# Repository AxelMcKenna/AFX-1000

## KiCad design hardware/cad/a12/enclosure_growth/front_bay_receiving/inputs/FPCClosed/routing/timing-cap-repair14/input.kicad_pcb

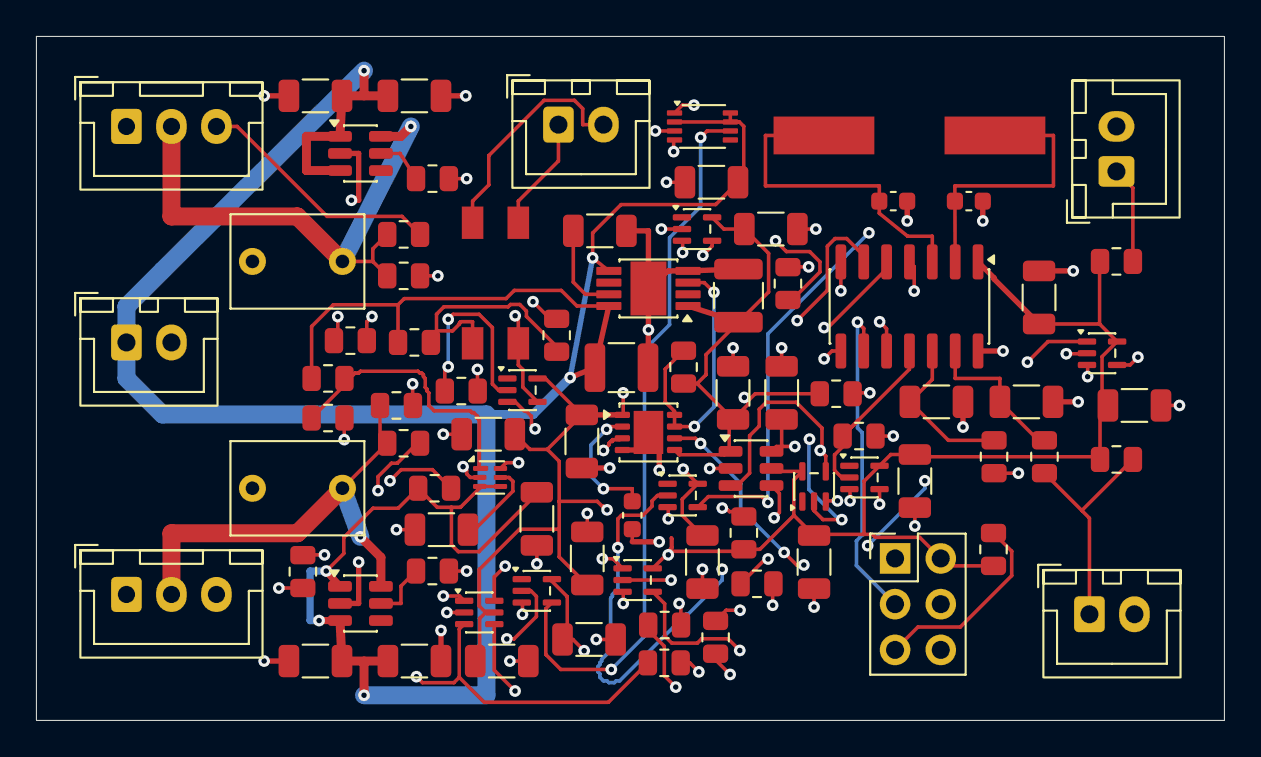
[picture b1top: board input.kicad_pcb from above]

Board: 4 copper layers, 66.0 x 38.0 mm, 84 parts (0 on the bottom side), 45 nets.

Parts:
C1, C2: 10uF 25V C3225X7R1E106K250AC; Capacitor_SMD__C_1210_3225Metric
C3, C14, C22, C23: 10nF 50V C0G C1206C103J5GACTU; Capacitor_SMD__C_1206_3216Metric
C4, C5, C6, C8, C9, C10, C11, C12, C13, C15, C16, C17, C18, C19, C24: 100nF 25V C0G C1206C104J3GACTU; Capacitor_SMD__C_1206_3216Metric
C7: 2.7nF 50V C0G5% C0603C272J5GACTU; Capacitor_SMD__C_0603_1608Metric
C20, C21: 15pF 50V C0G5% C0603C150J5GACTU; Capacitor_SMD__C_0603_1608Metric
C201, C202, C301, C302: 100nF25V C0G5% C1206C104J3GACTU; Capacitor_SMD__C_1206_3216Metric
C203, C303: 1uF63V10% WIMA MKS2C041001F00KSSD; Capacitor_THT__C_Rect_L7.2mm_W5.0mm_P5.00mm
J2, J3, J4, J201: JST B2B-XH-A / XHP-2 / SXH-001T-P0.6; Connector_JST__JST_XH_B2B-XH-A_1x02_P2.50mm_Vertical
J5: AVRISP2x3 target-powered3.3V sense ONLY; Connector_PinHeader_2.54mm__PinHeader_2x03_P2.54mm_Vertical
J202, J203: JST B3B-XH-A / XHP-3 / SXH-001T-P0.6; Connector_JST__JST_XH_B3B-XH-A_1x03_P2.50mm_Vertical
R1, R16, R17, R21, R23: 1k 0.1%25ppm TNPW08051K00BEEA; Resistor_SMD__R_0805_2012Metric
R2, R6, R10, R13, R202, R302: 10k 0.1%25ppm TNPW080510K0BEEA; Resistor_SMD__R_0805_2012Metric
R3, R4, R5, R7, R14, R15: 47k 0.1%25ppm TNPW080547K0BEEA; Resistor_SMD__R_0805_2012Metric
R8: 68k 0.1%25ppm TNPW080568K0BEEA; Resistor_SMD__R_0805_2012Metric
R9: 39k 0.1%25ppm TNPW080539K0BEEA; Resistor_SMD__R_0805_2012Metric
R11: 56.2k 0.1%25ppm TNPW080556K2BEEA; Resistor_SMD__R_0805_2012Metric
R12, R24, R201, R203, R301, R303: 100k 0.1%25ppm TNPW0805100KBEEA; Resistor_SMD__R_0805_2012Metric
R20, R22: 20k 0.1%25ppm TNPW080520K0BEEA; Resistor_SMD__R_0805_2012Metric
U1: ATtiny84A-SSUR; Package_SO__SOIC-14_3.9x8.7mm_P1.27mm
U2: TPS7A1633DGNR; TI_DGN0008C
U3: SN74LVC2G17DCKR; Package_TO_SOT_SMD__SOT-363_SC-70-6
U4: TPS3431SDRBR; Package_SON__VSON-8-1EP_3x3mm_P0.65mm_EP1.65x2.4mm
U5: SN74AUP1G17DCKR; Package_TO_SOT_SMD__SOT-353_SC-70-5
U6: SN74LVC1T45DBVR; Package_TO_SOT_SMD__SOT-23-6
U7: SN74LVC1G14DCKR; Package_TO_SOT_SMD__SOT-353_SC-70-5
U8: SN74LVC1G74DCUR; TI_DCU0008A
U9: TPS389001DSET; Package_SON__WSON-6_1.5x1.5mm_P0.5mm
U10, U11: SN74LVC1G17DCKR; Package_TO_SOT_SMD__SOT-353_SC-70-5
U12, U13: SN74LVC1G08DCKR; Package_TO_SOT_SMD__SOT-353_SC-70-5
U14: SN74LVC1G06DCKR; Package_TO_SOT_SMD__SOT-353_SC-70-5
U15: TLP175A(TPL,E); RMX_FH02__TLP175A_11-4M1S_Receiving
U16: SN74LVC1G34DCKR; Package_TO_SOT_SMD__SOT-353_SC-70-5
U201, U301: TPS2553DBVR-1; Package_TO_SOT_SMD__SOT-23-6
X1: ABLS-4.000MHZ-12-D4Y-T; RMX_FH02__ABLS_Manufacturer_Land

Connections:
/E28_POWER_RUN: J4.2, U15.6
/FAN5V_IN: C1.1, C10.1, C11.1, C12.1, C13.1, C15.1, C201.1, C202.1, C301.1, C302.1, J201.1, R1.1, R10.1, R11.1, U2.5, U2.8, U6.6, U7.5, U8.2, U8.7, U8.8, U9.3, U9.4, U10.5, U201.1, U201.3, U301.1, U301.3
/FAN_L_5V: C203.1, J202.2, R202.1, R203.1, U201.6
/FAN_L_ILIM: R201.1, U201.5
/FAN_L_TACH: J202.3, R14.1, R202.2, U3.1
/FAN_R_5V: C303.1, J203.2, R302.1, R303.1, U301.6
/FAN_R_ILIM: R301.1, U301.5
/FAN_R_TACH: J203.3, R15.1, R302.2, U3.3
/FAULT_CLK: U7.4, U8.1
/GND: C1.2, C2.2, C3.2, C4.2, C5.2, C6.2, C7.2, C8.2, C9.2, C10.2, C11.2, C12.2, C13.2, C14.2, C15.2, C16.2, C17.2, C18.2, C19.2, C20.2, C21.2, C22.2, C23.2, C24.2, C201.2, C202.2, C203.2, C301.2, C302.2, C303.2, J2.2, J3.2, J5.6, J201.2, J202.1, J203.1, R3.2, R4.2, R8.2, R9.2, R12.2, R13.2, R14.2, R15.2, R24.2, R201.2, R203.2, R301.2, R303.2, U1.14, U2.4, U2.9, U3.2, U4.4, U4.9, U5.3, U6.2, U7.3, U8.4, U9.2, U10.3, U11.3, U12.3, U13.3, U14.3, U16.3, U201.2, U301.2
/HEALTH_AND_WD: U12.4, U13.1
/HEARTBEAT: R4.1, U1.11, U16.2
/HEARTBEAT_FAST: U4.6, U16.4
/HW_NOFAULT: U11.4, U13.2
/HW_NOFAULT_5: R9.1, U8.3, U11.2
/ISP_MISO: J5.1, U1.8
/ISP_MOSI: J5.4, U1.7
/ISP_SCK: J5.3, U1.9
/LDO_DELAY: C3.1, U2.7
/LEAF_PERMISSION: R13.1, U13.4, U14.2
/LED_A: R1.2, R2.1, U15.1
/LED_K: R2.2, U14.4, U15.3
/MCU_HEALTH: R3.1, U1.6, U12.1
/MCU_RESET_N: J5.5, R6.2, U1.4
/MCU_TACH_L: R16.2, U1.10
/MCU_TACH_R: R17.2, U1.5
/P03_POWER_RUN: J4.1, U15.4
/RAW_CLEAR_FAST: U8.6, U10.4
/RAW_CLEAR_N: R10.2, U9.6, U10.2
/RAW_POR_CT: C14.1, U9.5
/RAW_POR_SENSE: R11.2, R12.1, U9.1
/TACH_L_BUF: R16.1, U3.6
/TACH_R_BUF: R17.1, U3.4
/TEMP_L_ADC: C22.1, R21.2, U1.13
/TEMP_L_NODE: J2.1, R20.2, R21.1
/TEMP_R_ADC: C23.1, R23.2, U1.12
/TEMP_R_NODE: J3.1, R22.2, R23.1
/V3V3: C2.1, C4.1, C5.1, C6.1, C8.1, C9.1, C16.1, C17.1, C18.1, C19.1, C24.1, J5.2, R5.1, R6.1, R7.1, R20.1, R22.1, R24.1, U1.1, U2.1, U3.5, U4.1, U4.5, U5.5, U6.1, U6.5, U11.5, U12.5, U13.5, U14.5, U16.5
/WD_CWD: C7.1, U4.2
/WD_EN: R7.2, U4.3
/WD_OK: R5.2, U2.3, U4.7, U4.8, U5.2
/WD_OK_5: R8.1, U6.4, U7.2
/WD_OK_FAST: U5.4, U6.3, U12.2
/XTAL1: C20.1, U1.2, X1.1
/XTAL2: C21.1, U1.3, X1.2

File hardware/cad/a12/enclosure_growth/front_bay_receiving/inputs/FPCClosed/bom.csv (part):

Reference,Part_or_value,Footprint,Source,Note
U1,ATtiny84A-SSUR,FPC01:Package_SO__SOIC-14_3.9x8.7mm_P1.27mm,https://ww1.microchip.com/downloads/en/DeviceDoc/ATtiny24A-4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,"Microchip DS40002269A source bytes captured. External4MHz crystal; CPU4MHz, Timer1/8, ADC/64 per captured root firmware. 3mA VCC-pin current is receiving, NOT a transferable bare-external-clock table guarantee."
U2,TPS7A1633DGNR,FPC01:TI_DGN0008C,https://www.ti.com/lit/ds/symlink/tps7a16.pdf,"Fixed output: pin2 MUST remain unconnected. PG joins open-drain WD_OK; rising85..95% output threshold is not a precision3.3V monitor. All regulator caps same FRONT face, local direct ground in future layout."
U3,SN74LVC2G17DCKR,FPC01:Package_TO_SOT_SMD__SOT-363_SC-70-6,https://www.ti.com/lit/ds/symlink/sn74lvc2g17.pdf,5.5V tolerant Schmitt inputs/Ioff. Fan-side pullups follow switched5V in FP01; no always-on pullup phantom-feed.
U4,TPS3431SDRBR,FPC01:Package_SON__VSON-8-1EP_3x3mm_P0.65mm_EP1.65x2.4mm,https://www.ti.com/lit/ds/symlink/tps3431.pdf,"TI permits tying ENOUT/WDO. Timeout independently blocks permission and clocksRAW5latch; it doesNOTdriveMCURESET, because startupENOUTLOW would createEXTRF and conflictwithcleanPOR firmware. Watchdogretry MUST NOT reclosecontact."
U5,SN74AUP1G17DCKR,FPC01:Package_TO_SOT_SMD__SOT-353_SC-70-5,https://www.ti.com/lit/ds/symlink/sn74aup1g17.pdf,
U6,SN74LVC1T45DBVR,FPC01:Package_TO_SOT_SMD__SOT-23-6,https://www.ti.com/lit/ds/symlink/sn74lvc1t45.pdf,A-to-B; either supply atGND isolates both ports. RAW5 B pulldown forces fault on complete3.3V loss; intermediate-rail behavior remains receiving.
U7,SN74LVC1G14DCKR,FPC01:Package_TO_SOT_SMD__SOT-353_SC-70-5,https://www.ti.com/lit/ds/symlink/sn74lvc1g14.pdf,
U8,SN74LVC1G74DCUR,FPC01:TI_DCU0008A,https://www.ti.com/lit/ds/symlink/sn74lvc1g74.pdf,IndependentRAW5-powered positive-edge latch; D=1. First watchdog failure storesQ=1/Q_N=0 until RAW5 power-cycle clear. 3.3V-only resets cannot intentionally clear it.
U9,TPS389001DSET,FPC01:Package_SON__WSON-6_1.5x1.5mm_P0.5mm,https://www.ti.com/lit/ds/symlink/tps3890.pdf,"Dedicatedrawpower-cycle clear nominal1.7963V; assertion/deassertion and1.65V latch retention crossover must be characterized. CT delays clear RELEASE, not fault capture."
U10,SN74LVC1G17DCKR,FPC01:Package_TO_SOT_SMD__SOT-353_SC-70-5,https://www.ti.com/lit/ds/symlink/sn74lvc1g17.pdf,
U11,SN74LVC1G17DCKR,FPC01:Package_TO_SOT_SMD__SOT-353_SC-70-5,https://www.ti.com/lit/ds/symlink/sn74lvc1g17.pdf,
U12,SN74LVC1G08DCKR,FPC01:Package_TO_SOT_SMD__SOT-353_SC-70-5,https://www.ti.com/lit/ds/symlink/sn74lvc1g08.pdf,2.0V VIH applies over actual3.0..3.6V supply row. All inputs have active push-pull drivers; rawopen-drain WD_OK is Schmittconditioned first.
U13,SN74LVC1G08DCKR,FPC01:Package_TO_SOT_SMD__SOT-353_SC-70-5,https://www.ti.com/lit/ds/symlink/sn74lvc1g08.pdf,2.0V VIH applies over actual3.0..3.6V supply row. All inputs have active push-pull drivers; rawopen-drain WD_OK is Schmittconditioned first.
U14,SN74LVC1G06DCKR,FPC01:Package_TO_SOT_SMD__SOT-353_SC-70-5,https://www.ti.com/lit/ds/symlink/sn74lvc1g06.pdf,
U16,SN74LVC1G34DCKR,FPC01:Package_TO_SOT_SMD__SOT-353_SC-70-5,https://www.ti.com/lit/ds/symlink/sn74lvc1g34.pdf,
U15,"TLP175A(TPL,E)",FPC01:RMX_FH02__TLP175A_11-4M1S_Receiving,https://toshiba.semicon-storage.com/info/TLP175A_datasheet_e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,Normally-open isolated contact ONLY P03J106.3→E28J5.3. 1/3LED and4/6contact exact pins. Recommendedambient≤65°C. No E28_MASTER_ENABLE connection.
X1,ABLS-4.000MHZ-12-D4Y-T,FPC01:RMX_FH02__ABLS_Manufacturer_Land,https://abracon.com/Resonators/abls.pdf,4MHzfundamental/CL12pF/−40..85C/initial±30ppm/temp±30ppm. Manufacturerland5.6x2.1mm/9.5mmcentres. 15pF+15pF assumes4.5pFstray; drive/startup/complete±0.1%clock requires receiving tests.
R1,1k 0.1%25ppm TNPW08051K00BEEA,FPC01:Resistor_SMD__R_0805_2012Metric,https://www.vishay.com/docs/28758/tnpw_e3.pdf,Complete±3%; feed branch includes shunt current once.
R2,10k 0.1%25ppm TNPW080510K0BEEA,FPC01:Resistor_SMD__R_0805_2012Metric,https://www.vishay.com/docs/28758/tnpw_e3.pdf,"Complete±3%; across LED, not merely gate pulldown. Ioff10uA creates≤.103VLED in settled model."
R3,47k 0.1%25ppm TNPW080547K0BEEA,FPC01:Resistor_SMD__R_0805_2012Metric,https://www.vishay.com/docs/28758/tnpw_e3.pdf,DefaultOFF duringMCUreset/input state.
R4,47k 0.1%25ppm TNPW080547K0BEEA,FPC01:Resistor_SMD__R_0805_2012Metric,https://www.vishay.com/docs/28758/tnpw_e3.pdf,No floatingWDI whileMCUreset.
R5,47k 0.1%25ppm TNPW080547K0BEEA,FPC01:Resistor_SMD__R_0805_2012Metric,https://www.vishay.com/docs/28758/tnpw_e3.pdf,Open-drainwatchdog/PG pullup.
R6,10k 0.1%25ppm TNPW080510K0BEEA,FPC01:Resistor_SMD__R_0805_2012Metric,https://www.vishay.com/docs/28758/tnpw_e3.pdf,MCURESET externalpullup; internal30..60k table at5.5V is not our full3.3V bound. ExternalwatchdogdoesNOTdriveRESET; avoidsstartupEXTRF.
R7,47k 0.1%25ppm TNPW080547K0BEEA,FPC01:Resistor_SMD__R_0805_2012Metric,https://www.vishay.com/docs/28758/tnpw_e3.pdf,WDalwaysenabled; manufacturing must not leave bypass fitted.
R8,68k 0.1%25ppm TNPW080568K0BEEA,FPC01:Resistor_SMD__R_0805_2012Metric,https://www.vishay.com/docs/28758/tnpw_e3.pdf,Complete±3%; 1T45off2uA+G14input5uA gives≤.49028V.
R9,39k 0.1%25ppm TNPW080539K0BEEA,FPC01:Resistor_SMD__R_0805_2012Metric,https://www.vishay.com/docs/28758/tnpw_e3.pdf,Complete±3%; rawFFIoff10uA+G17input5uA gives≤.60255V.
R10,10k 0.1%25ppm TNPW080510K0BEEA,FPC01:Resistor_SMD__R_0805_2012Metric,https://www.vishay.com/docs/28758/tnpw_e3.pdf,SupervisorOCpullup; Schmitt before ordinaryCLR input.
R11,56.2k 0.1%25ppm TNPW080556K2BEEA,FPC01:Resistor_SMD__R_0805_2012Metric,https://www.vishay.com/docs/28758/tnpw_e3.pdf,Complete±1% receiving.
R12,100k 0.1%25ppm TNPW0805100KBEEA,FPC01:Resistor_SMD__R_0805_2012Metric,https://www.vishay.com/docs/28758/tnpw_e3.pdf,Complete±1% receiving.
R13,10k 0.1%25ppm TNPW080510K0BEEA,FPC01:Resistor_SMD__R_0805_2012Metric,https://www.vishay.com/docs/28758/tnpw_e3.pdf,LEDsinkdefaultOFF whenlogicoutputs highZ;10uAoutputIoff+5uAinputleak→≤.1545V givencomplete±3%R. Intermediatepowerstillrequirescharacterization.
R14,47k 0.1%25ppm TNPW080547K0BEEA,FPC01:Resistor_SMD__R_0805_2012Metric,https://www.vishay.com/docs/28758/tnpw_e3.pdf,Receiveropen-wiredefaultLOW; sourcepullup current already inFP01ledger.
R15,47k 0.1%25ppm TNPW080547K0BEEA,FPC01:Resistor_SMD__R_0805_2012Metric,https://www.vishay.com/docs/28758/tnpw_e3.pdf,Receiveropen-wiredefaultLOW; noextraalways-on5Vpullup.
R16,1k 0.1%25ppm TNPW08051K00BEEA,FPC01:Resistor_SMD__R_0805_2012Metric,https://www.vishay.com/docs/28758/tnpw_e3.pdf,Edge/ISR error must be measured with this actualRC.
R17,1k 0.1%25ppm TNPW08051K00BEEA,FPC01:Resistor_SMD__R_0805_2012Metric,https://www.vishay.com/docs/28758/tnpw_e3.pdf,Edge/ISR error must be measured with this actualRC.
R20,20k 0.1%25ppm TNPW080520K0BEEA,FPC01:Resistor_SMD__R_0805_2012Metric,https://www.vishay.com/docs/28758/tnpw_e3.pdf,Complete±.5% receiving; exact203AT-2current/thermalcoupling unqualified.
R21,1k 0.1%25ppm TNPW08051K00BEEA,FPC01:Resistor_SMD__R_0805_2012Metric,https://www.vishay.com/docs/28758/tnpw_e3.pdf,Complete±3% receiving; totalADC+capacitorleak±1.1uA receiving.
R22,20k 0.1%25ppm TNPW080520K0BEEA,FPC01:Resistor_SMD__R_0805_2012Metric,https://www.vishay.com/docs/28758/tnpw_e3.pdf,Complete±.5% receiving.
R23,1k 0.1%25ppm TNPW08051K00BEEA,FPC01:Resistor_SMD__R_0805_2012Metric,https://www.vishay.com/docs/28758/tnpw_e3.pdf,Complete±3% receiving.
R24,100k 0.1%25ppm TNPW0805100KBEEA,FPC01:Resistor_SMD__R_0805_2012Metric,https://www.vishay.com/docs/28758/tnpw_e3.pdf,Complete±3% minimum-loadbleed:≥31.4uA at3.234V keepsLDOabove10uAaccuracycondition evenifMCU/sensorsquiet.
C1,10uF 25V C3225X7R1E106K250AC,FPC01:Capacitor_SMD__C_1210_3225Metric,https://product.tdk.com/en/search/capacitor/ceramic/mlcc/inf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,RequiredlocalFRONTinputcap; effective≥.1uF (project≥3uF receiving) acrossallcorners.
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
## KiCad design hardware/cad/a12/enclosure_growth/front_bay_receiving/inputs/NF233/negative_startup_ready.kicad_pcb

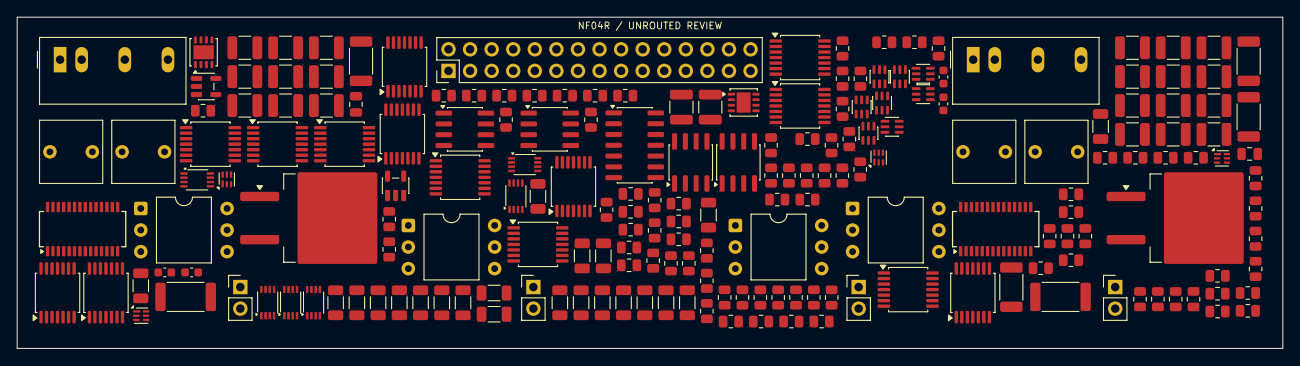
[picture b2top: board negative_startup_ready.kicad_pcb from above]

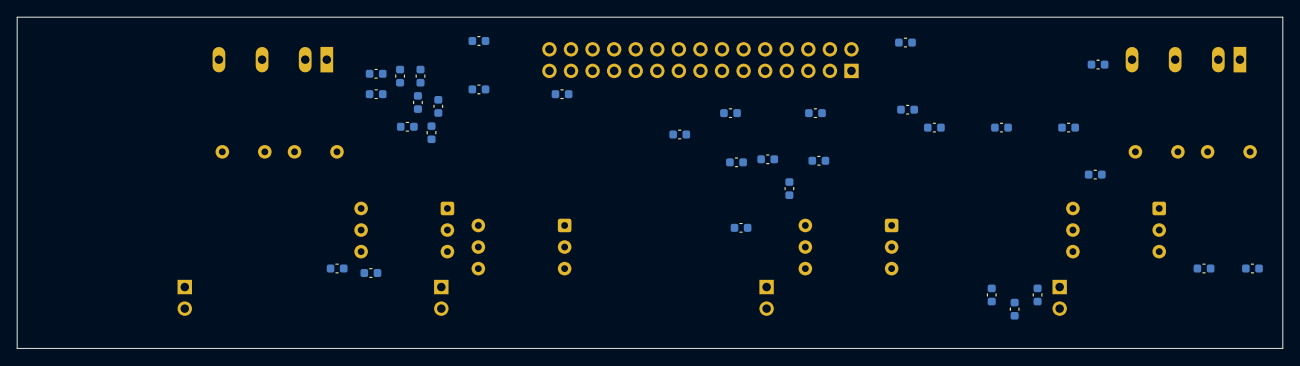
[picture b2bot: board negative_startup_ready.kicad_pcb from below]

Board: 4 copper layers, 149.0 x 39.0 mm, 233 parts (33 on the bottom side), 194 nets, no tracks yet.

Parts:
C1: 56nF C0G COMPLETE +/-10% RECEIVING; Capacitor_SMD__C_0805_2012Metric
C2: 33nF C0G COMPLETE +/-10% RECEIVING; Capacitor_SMD__C_0805_2012Metric
C3, C12, C39, C55, C56, C57, C58, C59, C60, C61, C62, C63, C64, C65, C66, C67, C68, C69, C70, C71, C72, C73, C74, C75, C76, C77, C78, C79, C80, C81, C82, C83, C84, C85, C86, C87, C88: 100nF 50V X7R10% C0603C104K5RACTU - bypass effect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; Capacitor_SMD__C_0603_1608Metric
C4, C31: 10uF 25V X7R MODULE INPUT FILTER/EFFECTIVE/INRUSH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; Capacitor_SMD__C_1206_3216Metric
C5, C32: 1uF 50V X7R MODULE OUTPUT FILTER/EFFECTIVE HOLD; Capacitor_SMD__C_1206_3216Metric
C6, C33: 1uF 25V X7R LTC4261 local VIN effective HOLD; Capacitor_SMD__C_1206_3216Metric
C7, C9, C11, C13, C34, C36, C38, C40: 100nF 25V C0G C1206C104J3GACTU; Capacitor_SMD__C_1206_3216Metric
C8, C10, C35, C37: 10nF 50V C0G COMPLETE10% TIMING RECEIVING; Capacitor_SMD__C_1206_3216Metric
C14, C15, C16, C17, C18, C19, C20, C21, C22, C23, C24, C25, C41, C42, C43, C44, C45, C46, C47, C48, C49: 100nF 50V C0G C1210C104J5GACTU - COMPLETE10% RAMP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; Capacitor_SMD__C_1210_3225Metric
C26, C27, C50, C51: 2.2uF 63V PET5% MKS2C042201K00JSSD - COMPLETE10% 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; Capacitor_THT__C_Rect_L7.2mm_W7.2mm_P5.00mm_FKS2_FKP2_MKS2_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
C28, C30, C52, C54: 47nF 50V C0G C1206C473J5GACTU; Capacitor_SMD__C_1206_3216Metric
C29, C53: 100nF 50V C0G C1210C104J5GACTU; Capacitor_SMD__C_1210_3225Metric
J1: NEW NF03C CONTROL/KELVIN INTERFACE - physical con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; Connector_PinHeader_2.54mm__PinHeader_2x15_P2.54mm_Vertical
J2: N19 NEW FORCE IN/OUT - connector and harness unse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; Connector_PinHeader_2.54mm__PinHeader_1x02_P2.54mm_Vertical
J3: N19 E28 BANK GATE/COMMON CLAMP - physical interfa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; Connector_PinHeader_2.54mm__PinHeader_1x02_P2.54mm_Vertical
J4: N12 NEW FORCE IN/OUT - connector and harness unse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; Connector_PinHeader_2.54mm__PinHeader_1x02_P2.54mm_Vertical
J5: N12 E28 BANK GATE/COMMON CLAMP - physical interfa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; Connector_PinHeader_2.54mm__PinHeader_1x02_P2.54mm_Vertical
Q1, Q2: CSD19536KTT; Package_TO_SOT_SMD__TO-263-2
R1, R2, R8, R9: 10k; Resistor_SMD__R_0805_2012Metric
R3, R10: 47k; Resistor_SMD__R_0805_2012Metric
R4, R11: 383ohm COMPLETE +/-3% RECEIVING; Resistor_SMD__R_0805_2012Metric
R5, R12: 10k COMPLETE +/-3% RECEIVING; Resistor_SMD__R_0805_2012Metric
R6, R7, R13, R14: 220ohm COMPLETE +/-3% RECEIVING; Resistor_SMD__R_0805_2012Metric
R15, R16, R17, R18, R19, R20, R21, R22: 47k 3% TOTAL RECEIVING; Resistor_SMD__R_0805_2012Metric
R23: 160000ohm COMPLETE0.1% RECEIVING; Resistor_SMD__R_0805_2012Metric
R24, R41, R63, R65, R80, R82: 10k COMPLETE0.1% RECEIVING; Resistor_SMD__R_0805_2012Metric
R25, R49: 8660ohm COMPLETE0.1% RECEIVING; Resistor_SMD__R_0805_2012Metric
R26, R50: 35.7ohm COMPLETE0.1% RECEIVING; Resistor_SMD__R_0805_2012Metric
R27, R31, R35, R44, R47, R51: 100k COMPLETE0.1% RECEIVING; Resistor_SMD__R_0805_2012Metric
R28, R32, R36, R37, R38, R39, R45, R48, R52, R53, R54, R55, R59, R76: 10k COMPLETE3% RECEIVING; Resistor_SMD__R_0805_2012Metric
R29, R46: 2000ohm COMPLETE0.1% RECEIVING; Resistor_SMD__R_0805_2012Metric
R30: 40.2ohm COMPLETE0.1% RECEIVING; Resistor_SMD__R_0805_2012Metric
R33: 6040ohm COMPLETE0.1% RECEIVING; Resistor_SMD__R_0805_2012Metric
R34: 75ohm COMPLETE0.1% RECEIVING; Resistor_SMD__R_0805_2012Metric
R40: 102000ohm COMPLETE0.1% RECEIVING; Resistor_SMD__R_0805_2012Metric
R42: 10700ohm COMPLETE0.1% RECEIVING; Resistor_SMD__R_0805_2012Metric
R43: 169ohm COMPLETE0.1% RECEIVING; Resistor_SMD__R_0805_2012Metric
R56, R57, R73, R74: 392ohm 1% CRCW2010392RFKEF - COMPLETE3% RECEIVING; Resistor_SMD__R_2010_5025Metric
R58, R60, R61, R66, R67, R68, R75, R77, R78, R83, R84, R85: 47k COMPLETE3% RECEIVING; Resistor_SMD__R_0805_2012Metric
R62, R79: 30.4k COMPLETE0.1% RECEIVING; Resistor_SMD__R_0805_2012Metric
R64, R81: 78.7k COMPLETE0.1% RECEIVING; Resistor_SMD__R_0805_2012Metric
R69: 0.33ohm COMPLETE5% SHUNT RECEIVING; Resistor_SMD__R_2512_6332Metric
R70, R87: 10ohm COMPLETE3% RECEIVING; Resistor_SMD__R_0805_2012Metric
R71, R88: 1M; Resistor_SMD__R_0805_2012Metric
R72: 27ohm COMPLETE3% RECEIVING; Resistor_SMD__R_0805_2012Metric
R86: 0.12ohm COMPLETE5% SHUNT RECEIVING; Resistor_SMD__R_2512_6332Metric
R89: 39ohm COMPLETE3% RECEIVING; Resistor_SMD__R_0805_2012Metric
U1, U2, U7, U8: SN74AUP1G74DCUR; TI_DCU0008A
U3, U9: TPS3431SDRBR; Package_SON__VSON-8-1EP_3x3mm_P0.65mm_EP1.65x2.4mm
U4, U10: SN74LVC1G06DBVR; Package_TO_SOT_SMD__SOT-23-5_LocalSilk
U5, U6, U11, U12: TLP4590AF(F; Package_DIP__DIP-6_W10.16mm
U13: OPA2333AID; Package_SO__SOIC-8_3.9x4.9mm_P1.27mm
U14: TLV1822DR; Package_SO__SOIC-8_3.9x4.9mm_P1.27mm
U15: TLV1824DR; Package_SO__SOIC-14_3.9x8.7mm_P1.27mm
U16, U27: SN74LVC2T45DCUR; TI_DCU0008A
U17, U22: TMR 1-1215; Converter_DCDC__Converter_DCDC_TRACO_TMR-1-xxxx_Single_THT
U18, U23: LTC4261IGN#PBF; Package_SO__SSOP-28_3.9x9.9mm_P0.635mm
U19, U24: ISO7721FDR; Package_SO__SOIC-8_3.9x4.9mm_P1.27mm
U20, U21, U25, U26: TPS389001DSET; Package_SON__WSON-6_1.5x1.5mm_P0.5mm
U28, U29, U30, U31, U32, U33, U34, U49: SN74AUP2G14DCKR; Package_TO_SOT_SMD__SOT-363_SC-70-6_LocalSilk
U35, U36, U37, U38, U39, U40, U41, U42, U43, U44: SN74HCS08PWR; Package_SO__TSSOP-14_4.4x5mm_P0.65mm
U45, U46: SN74HCS32PWR; Package_SO__TSSOP-14_4.4x5mm_P0.65mm
U47, U48: SN74HCS14PWR; Package_SO__TSSOP-14_4.4x5mm_P0.65mm

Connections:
AGND: C1.2, C2.2, C3.2, C4.2, C12.2, C31.2, C39.2, C55.2, C56.2, C57.2, C58.2, C59.2, C60.2, C61.2, C62.2, C63.2, C64.2, C65.2, C66.2, C67.2, C68.2, C69.2, C70.2, C71.2, C72.2, C73.2, C74.2, C75.2, C76.2, C77.2, C78.2, C79.2, C80.2, C81.2, C82.2, C83.2, C84.2, C85.2, C86.2, C87.2, C88.2, J1.2, R3.2, R10.2, R15.2, R16.2, R17.2, R18.2, R19.2, R20.2, R21.2, R22.2, R27.2, R31.2, R35.2, R44.2, R47.2, R51.2, R59.2, R61.2, R67.2, R68.2, R76.2, R78.2, R84.2, R85.2, U1.4, U2.4, U3.4, U3.9, U4.3, U7.4, U8.4, U9.4, U9.9, U10.3, U13.3, U13.4, U13.5, U14.4, U15.12, U16.4, U17.1, U19.5, U22.1, U24.5, U27.4, U28.2, U29.2, U30.2, U31.2, U32.2, U33.2, U34.2, U35.7, U36.7, U37.7, U38.7, U39.7, U40.7, U41.7, U42.7, U43.7, U44.7, U45.7, U46.7, U46.12, U46.13, U47.7, U48.7, U48.11, U48.13, U49.2
AUX2V6: C56.1, C57.1, C58.1, C59.1, C60.1, C61.1, C62.1, C63.1, C64.1, C65.1, C66.1, C67.1, C68.1, C69.1, C70.1, C71.1, C72.1, C73.1, C74.1, C75.1, C76.1, C77.1, C78.1, C79.1, C80.1, C81.1, C82.1, C83.1, C84.1, C85.1, C86.1, C87.1, C88.1, J1.1, R1.1, R2.1, R8.1, R9.1, R37.1, R38.1, R39.1, R53.1, R54.1, R55.1, U1.7, U1.8, U2.2, U2.7, U2.8, U3.1, U7.7, U7.8, U8.2, U8.7, U8.8, U9.1, U13.8, U14.8, U15.3, U16.1, U16.5, U27.8, U28.5, U29.5, U30.5, U31.5, U32.5, U33.5, U34.5, U35.14, U36.14, U37.14, U38.14, U39.14, U40.14, U41.14, U42.14, U43.14, U44.14, U45.14, U46.14, U47.14, U48.14, U49.5
AUX_VALID: J1.5, R16.1, U35.1
DIG5_FORCE: C3.1, C12.1, C39.1, C55.1, J1.3, R4.1, R11.1, U4.5, U10.5, U16.8, U19.8, U24.8, U27.1, U27.5
E28_COMBINED_FAULT_REQUEST: J1.14, U34.4
E28_COMBINED_FAULT_REQUEST_BUFFER_MID: U34.3, U34.6
E28_COMBINED_FAULT_REQUEST_HCS: U34.1, U46.6
E28_NATIVE_FAULT_REQUEST: J1.13, U46.4
E28_NOT_FAULT: J1.15, R22.1, U44.4
GLOBAL_MASTER: J1.6, R15.1, U35.2
GLOBAL_VALID: U35.3, U35.5, U37.4, U38.5, U38.13, U40.12, U41.13
GUARDED_12V_FORCE: C4.1, C31.1, J1.4, U17.2, U22.2
N12_ARM: J1.24, R20.1, U30.1
N12_ARM_CONDITIONED: U30.4, U38.12, U39.1, U39.4, U40.13, U41.12
N12_ARM_CONDITIONED_BUFFER_MID: U30.3, U30.6
N12_BANK_CLAMP_GATE: R14.2, U12.4
N12_BANK_COMMON: J5.2, U12.6
N12_BANK_GATE: J5.1, R14.1
N12_BIAS_CT: C37.1, U25.5
N12_BIAS_HOST5: R84.1, U24.6, U27.3
N12_BIAS_RESET_N: R83.2, U24.3, U25.6, U26.6
N12_BIAS_SENSE: R79.2, R80.1, U25.1
N12_BIAS_VALID: J1.17, R85.1, U27.6, U43.13
N12_CG_SERIES: C52.1, R87.2
N12_CLAMPS_RELEASE: J1.28, R10.1, U10.2, U33.4
N12_CLAMPS_RELEASE_BUFFER_MID: U33.3, U33.6
N12_CLAMPS_RELEASE_HCS: U33.1, U42.3
N12_CLAMP_LED_A: R11.2, R12.1, U11.1
N12_CLAMP_LED_K: R12.2, U10.4, U12.2
N12_CLAMP_LED_MID: U11.2, U12.1
N12_COMPLETE: J1.27, U8.5, U39.12, U44.12
N12_COMPLETE_CLK: U8.1, U41.8
N12_COMPLETE_CLR_N: U8.6, U41.11
N12_CONTROLLER_ON: R77.1, U23.2, U24.2
N12_CR_TOP: C41.1, C42.1, C43.1, C44.1, C45.1, C46.1, C47.1, C48.1, C49.1, R89.2
N12_CWD: C2.1, U9.2
N12_DRAIN_SENSE: R88.2, U23.16
N12_E28_SRC: C41.2, C42.2, C43.2, C44.2, C45.2, C46.2, C47.2, C48.2, C49.2, J4.2, Q2.2, R88.1
N12_F0: U45.8, U45.12
N12_FAULT_REQUEST: J1.26, U45.11, U46.2
N12_FEED_MID: R73.2, R74.1
N12_F_OUTPUT: U39.11, U45.13
N12_F_SOURCE: U39.3, U45.9
N12_F_TIMEOUT: U39.8, U45.10
N12_F_WD_ARM: U39.6, U39.9
N12_INTVCC: C34.1, C36.1, C38.1, C40.1, R79.1, R83.1, U23.5, U23.6, U23.7, U23.8, U23.9, U23.22, U24.1, U25.3, U25.4, U26.3, U26.4
N12_ISO24: C32.1, R73.1, U22.4
N12_NOT_COMPLETE: U8.3, U9.5
N12_NOT_PERMIT: U7.3, U9.6
N12_NOT_READY: U39.13, U47.10
N12_NOT_SAFE: U39.2, U47.8
N12_NOT_WDO: U39.10, U47.12
N12_OUTPUT_OV_GOOD: R55.2, U15.13, U43.10, U44.2
N12_OUTPUT_QUALIFIED: U44.11, U48.5
N12_OUTPUT_UV_GOOD: R54.2, U15.14, U44.1
N12_OUT_INV: R41.1, R45.1, R48.1, U13.7
N12_OUT_OV_REF: R46.2, R47.1, U15.11
N12_OUT_OV_SENSE: R48.2, U15.10
N12_OUT_SUM: R40.2, R41.2, U13.6
N12_OUT_UV_REF: R43.2, R44.1, U15.8
N12_OUT_UV_RMID: R42.2, R43.1
N12_OUT_UV_SENSE: R45.2, U15.9
N12_OV_OK: J1.10, U43.5
N12_OV_SENSE: J1.12, R52.1
N12_P03_SRC: C32.2, C33.2, C34.2, C35.2, C36.2, C37.2, C38.2, C40.2, C50.2, C51.2, C52.2, C53.2, C54.2, J4.1, R75.2, R76.1, R77.2, R80.2, R82.2, R86.1, U22.6, U23.1, U23.3, U23.10, U23.11, U23.13, U23.23, U23.24, U23.25, U23.26, U23.27, U24.4, U25.2, U26.2
N12_PASS_CLAMP_GATE: R13.2, U11.4
N12_PASS_GATE: Q2.1, R13.1, R87.1, U23.15
N12_PASS_SOURCE: Q2.3, R86.2, U11.6, U23.14
N12_PCLR0: U40.11, U41.1, U42.1
N12_PCLR1: U41.3, U41.4
N12_PERMIT: U7.5, U16.3, U41.9
N12_PERMIT_CLR_N: U7.6, U41.6
N12_PERMIT_D: U7.2, U40.8
N12_PROTECTED: J1.29, R40.1
N12_RAMP: C50.1, C51.1, R89.1, U23.18
N12_READY: U41.10, U44.3, U44.13, U47.11
N12_RUN_HOST5: R78.1, U16.6, U24.7
N12_SAFE: U40.5, U41.5, U43.11, U47.9
N12_SOURCE_SAFE0: U43.6, U43.9
N12_SOURCE_SAFE1: U43.8, U43.12
N12_SOURCE_UV_GOOD: R53.2, U14.7, U43.4
N12_SOURCE_UV_REF: R50.2, R51.1, U14.6
N12_SOURCE_UV_RMID: R49.2, R50.1
N12_SOURCE_UV_SENSE: R52.2, U14.5
N12_SS: C53.1, U23.19
N12_START: J1.25, R21.1, U31.1
N12_START_ARMED: U40.3, U40.4
N12_START_CONDITIONED: U7.1, U31.4
N12_START_CONDITIONED_BUFFER_MID: U31.3, U31.6
N12_START_SAFE: U40.6, U40.9
N12_TMR: C54.1, U23.20
N12_VIN: C33.1, R74.2, R75.1, R81.1, U23.21
N12_VIN_VALID_CT: C35.1, U26.5
N12_VIN_VALID_SENSE: R81.2, R82.1, U26.1
N12_WDO: R8.2, U9.7, U40.2, U47.13
N12_WD_ARMED: R9.2, U9.8, U39.5, U40.1
N12_WD_ENABLE: U9.3, U38.11
N19_ARM: J1.18, R18.1, U28.1
N19_ARM_CONDITIONED: U28.4, U35.4, U35.9, U35.12, U37.5, U38.4
N19_ARM_CONDITIONED_BUFFER_MID: U28.3, U28.6
N19_BANK_CLAMP_GATE: R7.2, U6.4
N19_BANK_COMMON: J3.2, U6.6
N19_BANK_GATE: J3.1, R7.1
N19_BIAS_CT: C10.1, U20.5
N19_BIAS_HOST5: R67.1, U19.6, U27.2
N19_BIAS_RESET_N: R66.2, U19.3, U20.6, U21.6
N19_BIAS_SENSE: R62.2, R63.1, U20.1
N19_BIAS_VALID: J1.16, R68.1, U27.7, U42.13
N19_CG_SERIES: C28.1, R70.2
N19_CLAMPS_RELEASE: J1.22, R3.1, U4.2, U32.4
N19_CLAMPS_RELEASE_BUFFER_MID: U32.3, U32.6
N19_CLAMPS_RELEASE_HCS: U32.1, U38.8
N19_CLAMP_LED_A: R4.2, R5.1, U5.1
N19_CLAMP_LED_K: R5.2, U4.4, U6.2
N19_CLAMP_LED_MID: U5.2, U6.1
N19_COMPLETE: J1.21, U2.5, U36.4, U44.9
N19_COMPLETE_CLK: U2.1, U38.3
N19_COMPLETE_CLR_N: U2.6, U38.6
N19_CONTROLLER_ON: R60.1, U18.2, U19.2
N19_CR_TOP: C14.1, C15.1, C16.1, C17.1, C18.1, C19.1, C20.1, C21.1, C22.1, C23.1, C24.1, C25.1, R72.2
N19_CWD: C1.1, U3.2
N19_DRAIN_SENSE: R71.2, U18.16
N19_E28_SRC: C14.2, C15.2, C16.2, C17.2, C18.2, C19.2, C20.2, C21.2, C22.2, C23.2, C24.2, C25.2, J2.2, Q1.2, R71.1
N19_F0: U45.3, U45.4
N19_FAULT_REQUEST: J1.20, U45.6, U46.1
N19_FEED_MID: R56.2, R57.1
N19_F_OUTPUT: U36.6, U45.5
N19_F_SOURCE: U35.8, U45.1
N19_F_TIMEOUT: U36.3, U45.2
N19_F_WD_ARM: U35.11, U36.1
N19_INTVCC: C7.1, C9.1, C11.1, C13.1, R62.1, R66.1, U18.5, U18.6, U18.7, U18.8, U18.9, U18.22, U19.1, U20.3, U20.4, U21.3, U21.4
N19_ISO24: C5.1, R56.1, U17.4
N19_NOT_COMPLETE: U2.3, U3.5
N19_NOT_PERMIT: U1.3, U3.6
N19_NOT_READY: U36.5, U47.4
N19_NOT_SAFE: U35.10, U47.2
N19_NOT_WDO: U36.2, U47.6
N19_OUTPUT_OV_GOOD: R39.2, U15.1, U42.10, U43.2
N19_OUTPUT_QUALIFIED: U44.8, U48.3
N19_OUTPUT_UV_GOOD: R38.2, U15.2, U43.1
N19_OUT_INV: R24.1, R28.1, R32.1, U13.1
N19_OUT_OV_REF: R30.2, R31.1, U15.7
N19_OUT_OV_RMID: R29.2, R30.1
N19_OUT_OV_SENSE: R32.2, U15.6
N19_OUT_SUM: R23.2, R24.2, U13.2
N19_OUT_UV_REF: R26.2, R27.1, U15.4
N19_OUT_UV_RMID: R25.2, R26.1
N19_OUT_UV_SENSE: R28.2, U15.5
N19_OV_OK: J1.9, U42.5
N19_OV_SENSE: J1.11, R36.1
N19_P03_SRC: C5.2, C6.2, C7.2, C8.2, C9.2, C10.2, C11.2, C13.2, C26.2, C27.2, C28.2, C29.2, C30.2, J2.1, R58.2, R59.1, R60.2, R63.2, R65.2, R69.1, U17.6, U18.1, U18.3, U18.10, U18.11, U18.13, U18.23, U18.24, U18.25, U18.26, U18.27, U19.4, U20.2, U21.2
N19_PASS_CLAMP_GATE: R6.2, U5.4
N19_PASS_GATE: Q1.1, R6.1, R70.1, U18.15
N19_PASS_SOURCE: Q1.3, R69.2, U5.6, U18.14
N19_PCLR0: U37.6, U37.9, U38.9
N19_PCLR1: U37.8, U37.12
N19_PERMIT: U1.5, U16.2, U38.1
N19_PERMIT_CLR_N: U1.6, U37.11
N19_PERMIT_D: U1.2, U37.3
N19_PROTECTED: J1.23, R23.1
N19_RAMP: C26.1, C27.1, R72.1, U18.18
N19_READY: U38.2, U43.3, U44.10, U47.3
N19_RUN_HOST5: R61.1, U16.7, U19.7
N19_SAFE: U36.13, U37.13, U42.11, U47.1
N19_SOURCE_SAFE0: U42.6, U42.9
N19_SOURCE_SAFE1: U42.8, U42.12
N19_SOURCE_UV_GOOD: R37.2, U14.1, U42.4
N19_SOURCE_UV_REF: R34.2, R35.1, U14.2
N19_SOURCE_UV_RMID: R33.2, R34.1
N19_SOURCE_UV_SENSE: R36.2, U14.3
N19_SS: C29.1, U18.19
N19_START: J1.19, R19.1, U29.1
N19_START_ARMED: U36.8, U36.12
N19_START_CONDITIONED: U1.1, U29.4
N19_START_CONDITIONED_BUFFER_MID: U29.3, U29.6
N19_START_SAFE: U36.11, U37.1
N19_TMR: C30.1, U18.20
N19_VIN: C6.1, R57.2, R58.1, R64.1, U18.21
N19_VIN_VALID_CT: C8.1, U21.5
N19_VIN_VALID_SENSE: R64.2, R65.1, U21.1
N19_WDO: R1.2, U3.7, U36.10, U47.5
N19_WD_ARMED: R2.2, U3.8, U35.13, U36.9
N19_WD_ENABLE: U3.3, U35.6
NF_FAULT_REQUEST: U46.3, U46.5, U48.1
NF_NOT_OUTPUT_VALID: U46.8, U48.9
NF_NO_FAULT: U37.2, U37.10, U38.10, U40.10, U41.2, U42.2, U44.6
NF_OUTPUT_VALID: J1.30, U49.4
NF_OUTPUT_VALID_BUFFER_MID: U49.3, U49.6
NF_OUTPUT_VALID_HCS: U48.8, U49.1
NOT_N12_OUTPUT_QUALIFIED: U46.10, U48.6
NOT_N19_OUTPUT_QUALIFIED: U46.9, U48.4
NOT_NF_FAULT_REQUEST: U44.5, U48.2
PROTECT_REF: J1.8, R25.1, R29.1, R33.1, R42.1, R46.1, R49.1
RESET_REQUEST: J1.7, R17.1

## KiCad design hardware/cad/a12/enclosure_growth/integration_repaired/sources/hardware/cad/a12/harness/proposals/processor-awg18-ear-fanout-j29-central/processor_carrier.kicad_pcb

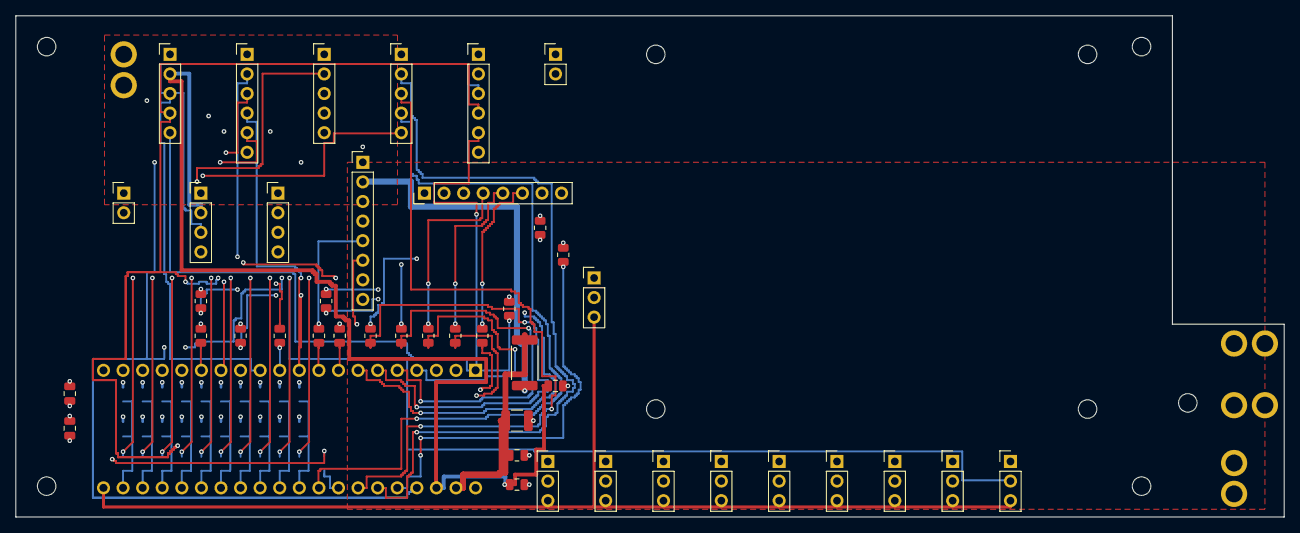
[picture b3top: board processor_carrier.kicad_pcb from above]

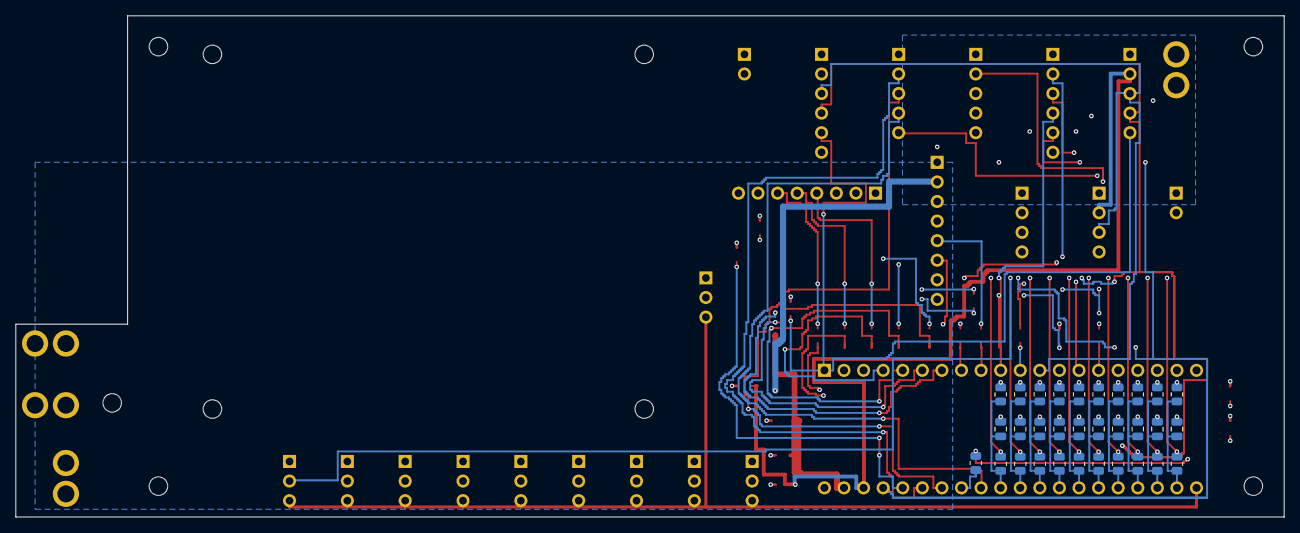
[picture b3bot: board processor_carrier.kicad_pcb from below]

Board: 4 copper layers, 164.5 x 65.0 mm, 88 parts (31 on the bottom side), 61 nets.

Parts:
C1: 22uF 25V X7R; C_1210_3225Metric
C2, C4, C6, C11, C12, C13, C14, C15, C16, C17, C18, C19, C20: 100nF 16V X7R; C_0805_2012Metric
C3: 1uF 16V X7R; C_0805_2012Metric
C5: 4.7uF 16V X7R; C_0805_2012Metric
H1, H2, H3, H4, H9: M2_CLEARANCE; M2_Insert_Clearance
H5, H6, H7, H8: M2_CLEARANCE; M2_Daughter
J1, J13, J14, J15: Alpha6715_AWG18_DIRECT_SOLDER_PROPOSAL; AWG18_Solder_2x1_P4mm_D2p2
J2, J4, J5: Header5; PinHeader_1x05_P2.54mm_Vertical
J3, J6: Header6; PinHeader_1x06_P2.54mm_Vertical
J7, J8: Header2; PinHeader_1x02_P2.54mm_Vertical
J9, J10: Header4; PinHeader_1x04_P2.54mm_Vertical
J11, J12: Header8; PinHeader_1x08_P2.54mm_Vertical
J20, J21, J22, J23, J24, J25, J26, J27, J28, J29: Header3; PinHeader_1x03_P2.54mm_Vertical
R1: 0.47R 1% 1W; R_2512_6332Metric
R2: 10k 1%; R_0805_2012Metric
R3, R4, R5, R6: 100k 1%; R_0805_2012Metric
R10, R11, R12, R13, R14, R15, R16, R17, R18, R19, R20: 33R 1%; R_0805_2012Metric
R31, R32, R33, R34, R35, R36, R37, R38, R39, R40: 1k 1%; R_0805_2012Metric
R41, R42, R43, R44, R45, R46, R47, R48, R49, R50: 1M 1%; R_0805_2012Metric
U1: DaisySeed3; Seed3_Socket40

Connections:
/5V_DIG: J1.1, J11.2, J13.1, J14.1, J15.1, R1.1
/ADC_DATA: J5.4, U1.32
/AGND: C1.2, C2.2, C3.2, C4.2, C5.2, C6.2, C11.2, C12.2, C13.2, C14.2, C15.2, C16.2, C17.2, C18.2, C19.2, C20.2, J1.2, J2.1, J3.1, J4.1, J5.1, J6.1, J7.1, J8.1, J9.1, J10.1, J11.1, J11.8, J12.1, J13.2, J14.2, J15.2, J20.1, J21.1, J22.1, J23.1, J24.1, J25.1, J26.1, J27.1, J28.1, J29.1, R3.2, R4.2, R5.2, R6.2, R41.2, R42.2, R43.2, R44.2, R45.2, R46.2, R47.2, R48.2, R49.2, R50.2, U1.20, U1.40
/ANALOG_OK: J4.4, J6.6
/ARMED: J3.5, R5.1, U1.37
/BCLK: J5.2, U1.35
/BYPASS_SENSE: J3.6, J4.3
/CODEC_RUN: J2.5, J6.5, R6.1, U1.1
/DAC_DATA: J5.5, R14.2
/DAC_DATA_SRC: R14.1, U1.33
/GAIN_REQ: J3.4, R4.1, U1.10
/HEARTBEAT: J3.2, U1.14
/INPUT_READY: J4.5, J7.2
/LED_BLANK: J11.7, R2.1, R13.2
/LED_BLANK_SRC: R13.1, U1.15
/LED_MOSI: J11.4, R12.2
/LED_MOSI_SRC: R12.1, U1.11
/LED_SCK: J11.5, R11.2
/LED_SCK_SRC: R11.1, U1.9
/LED_XLAT: J11.6, R10.2
/LED_XLAT_SRC: R10.1, U1.8
/MCU_PERMIT: J3.3, R3.1, U1.36
/MODE_SEND_RETURN: J4.2, J8.2
/POT_ADC_00: C11.1, R31.2, R41.1, U1.22
/POT_ADC_01: C12.1, R32.2, R42.1, U1.23
/POT_ADC_02: C13.1, R33.2, R43.1, U1.24
/POT_ADC_03: C14.1, R34.2, R44.1, U1.25
/POT_ADC_04: C15.1, R35.2, R45.1, U1.26
/POT_ADC_05: C16.1, R36.2, R46.1, U1.27
/POT_ADC_06: C17.1, R37.2, R47.1, U1.28
/POT_ADC_07: C18.1, R38.2, R48.1, U1.29
/POT_ADC_08: C19.1, R39.2, R49.1, U1.30
/POT_ADC_09: C20.1, R40.2, R50.1, U1.31
/POT_RAW_00: J20.2, R31.1
/POT_RAW_01: J21.2, R32.1
/POT_RAW_02: J22.2, R33.1
/POT_RAW_03: J23.2, R34.1
/POT_RAW_04: J24.2, R35.1
/POT_RAW_05: J25.2, R36.1
/POT_RAW_06: J26.2, R37.1
/POT_RAW_07: J27.2, R38.1
/POT_RAW_08: J28.2, R39.1
/POT_RAW_09: J29.2, R40.1
/SCL: J2.3, J6.3, J9.3, J10.3, U1.12
/SDA: J2.4, J6.4, J9.4, J10.4, U1.13
/SDMMC_CLK: J12.8, R20.2
/SDMMC_CLK_SRC: R20.1, U1.7
/SDMMC_CMD: J12.7, R19.2
/SDMMC_CMD_SRC: R19.1, U1.6
/SDMMC_D0: J12.3, R15.2
/SDMMC_D0_SRC: R15.1, U1.5
/SDMMC_D1: J12.4, R16.2
/SDMMC_D1_SRC: R16.1, U1.4
/SDMMC_D2: J12.5, R17.2
/SDMMC_D2_SRC: R17.1, U1.3
/SDMMC_D3: J12.6, R18.2
/SDMMC_D3_SRC: R18.1, U1.2
/SEED_VIN: C1.1, C2.1, R1.2, U1.39
/V3V3_ANALOG: C3.1, C4.1, J20.3, J21.3, J22.3, J23.3, J24.3, J25.3, J26.3, J27.3, J28.3, J29.3, U1.21
/V3V3_IO: C5.1, C6.1, J2.2, J6.2, J9.2, J10.2, J11.3, J12.2, R2.2, U1.38
/WS: J5.3, U1.34
